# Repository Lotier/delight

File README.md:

# DELIGHT Keyboard

**65+% keyboard assembled with only through hole components, including usb type-c**
**65+% means there is an extra row at the top for the Escape key just for the delight of programmers.

**[LICENSE](LICENSE)**

DELIGHT Keyboard is licensed under the [Creative Commons Attribution-NonCommercial 4.0 International License](https://creativecommons.org/licenses/by-nc/4.0/). , this board is adapted from [coseyfannitutti Discipline](https://github.com/coseyfannitutti/discipline) work.

This PCB design may be freely reproduced, modified, and manufactured for **PERSONAL USE ONLY** and may not be reproduced in physical form for public sale. 

# Keyboard Layout Editor
http://www.keyboard-layout-editor.com/#/
```
[{a:7},"esc"],
["`","1","2","3","4","5","6","7","8","9","0","-","=",{w:2},"backspace","home"],
[{w:1.5},"tab","q","w","e","r","t","y","u","i","o","p","[","]",{w:1.5},"\\","pgup"],
[{w:1.75},"cap","a","s","d","f","g","h","j","k","l",";","'",{w:2.25},"enter","pgdn"],
[{w:2.25},"shift","z","x","c","v","b","n","m",",",".","/",{w:1.75},"shift","up","end"],
[{w:1.25},"ctrl",{w:1.25},"win",{w:1.25},"alt",{w:6.25},"","alt","fn","ctrl","left","down","right"]
```

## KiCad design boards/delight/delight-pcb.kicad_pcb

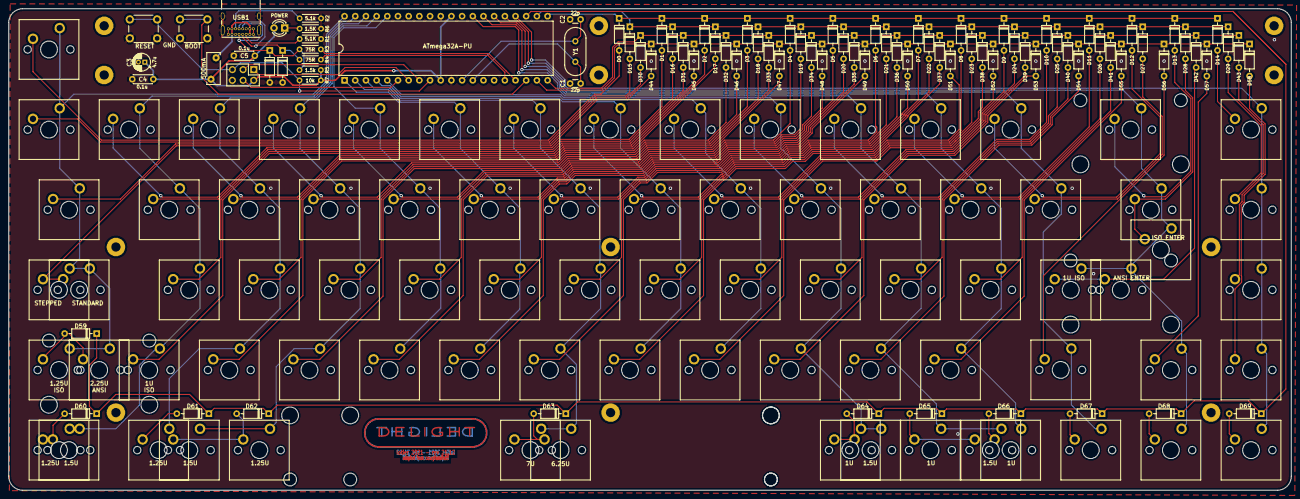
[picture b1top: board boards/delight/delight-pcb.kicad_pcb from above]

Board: 2 copper layers, 304.9 x 114.5 mm, 176 parts (0 on the bottom side), 107 nets.

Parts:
BOOT1: BOOT; SW_PUSH_6mm
C1, C2: 22p; C_Disc_D3.0mm_W1.6mm_P2.50mm
C3: 4.7u; CP_Radial_D4.0mm_P1.50mm
C4, C5: 0.1u; C_Disc_D4.3mm_W1.9mm_P5.00mm
D0, D1, D2, D3, D4, D5, D6, D7, D8, D9, D10, D11, D12, D13, D14, D15, D16, D17, D18, D19, D20, D21, D22, D23, D24, D25, D26, D27, D28, D29, D30, D31, D32, D33, D34, D35, D36, D37, D38, D39, D40, D41, D42, D43, D44, D45, D46, D47, D48, D49, D50, D51, D52, D53, D54, D55, D56, D57, D58, D59, D60, D61, D62, D63, D64, D65, D66, D67, D68, D69: D_DO-35_SOD27_P7.62mm_Horizontal
D70, D71: 3.6V; D_DO-35_SOD27_P7.62mm_Horizontal
F1: 500mA; Fuse_Bourns_MF-RHT050
J1: AVR-ISP-6; PinHeader_2x03_P2.54mm_Vertical
LED1: POWER; LED_D3.0mm
R1, R2: 5.1k; R_Axial_DIN0204_L3.6mm_D1.6mm_P5.08mm_Horizontal
R3, R4: 75R; R_Axial_DIN0204_L3.6mm_D1.6mm_P5.08mm_Horizontal
R5: 1.5k; R_Axial_DIN0204_L3.6mm_D1.6mm_P5.08mm_Horizontal
R6: 1.5K; R_Axial_DIN0204_L3.6mm_D1.6mm_P5.08mm_Horizontal
R7: 10k; R_Axial_DIN0204_L3.6mm_D1.6mm_P5.08mm_Horizontal
RESET1: RESET; SW_PUSH_6mm
ST13, ST42, ST59: Stabilizer_Cherry_MX_2u
ST63: 6.25U; Stabilizer_Cherry_MX_6.25u
ST63-2: 7U; Stabilizer_Cherry_MX_7u
SW0, SW1, SW2, SW3, SW4, SW5, SW6, SW7, SW8, SW9, SW10, SW11, SW12, SW14, SW15, SW16, SW17, SW18, SW19, SW20, SW21, SW22, SW23, SW24, SW25, SW26, SW27, SW29, SW31, SW32, SW33, SW34, SW35, SW36, SW37, SW38, SW39, SW40, SW41, SW42-2, SW43, SW45, SW46, SW47, SW48, SW49, SW50, SW51, SW52, SW53, SW54, SW55, SW57, SW58, SW64, SW65, SW66, SW67, SW68, SW69: KEYSW; SW_Cherry_MX_PCB_1.00u
SW13: KEYSW; SW_Cherry_MX_PCB_2.00u
SW28, SW30, SW60-2, SW62-2, SW64-2, SW65-2: KEYSW; SW_Cherry_MX_PCB_1.50u
SW28-2: KEYSW; SW_Cherry_MX_Plate_ISOEnter
SW42, SW59: KEYSW; SW_Cherry_MX_PCB_2.25u
SW44, SW56: KEYSW; SW_Cherry_MX_PCB_1.75u
SW44-2, SW59-2, SW60, SW61, SW62: KEYSW; SW_Cherry_MX_PCB_1.25u
SW63: KEYSW; SW_Cherry_MX_PCB_6.25u
SW63-2: KEYSW; SW_Cherry_MX_PCB_7.00u
U1: ATmega32A-PU; DIP-40_W15.24mm
USB1: USB_C_GCT_USB4085; USB_C_Receptacle_GCT_USB4085
Y1: Crystal; Crystal_HC49-4H_Vertical

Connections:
+5V: C3.1, C4.1, C5.1, F1.1, J1.2, LED1.2, R5.1, R7.1, U1.10, U1.30
D+: R4.1, U1.16
D-: R3.1, U1.17
GND: BOOT1.2, C1.2, C2.2, C3.2, C4.2, C5.2, D70.2, D71.2, J1.6, R1.1, R2.2, R6.2, RESET1.2, U1.11, U1.31, USB1.A1, USB1.A12, USB1.B1, USB1.B12, USB1.S1
MISO: J1.1, U1.7
MOSI: J1.4, U1.6
unnamed: C1.1, U1.13, Y1.1
unnamed: C2.1, U1.12, Y1.2
unnamed: D0.2, SW0.1
unnamed: D1.2, SW1.1
unnamed: D2.2, SW2.1
unnamed: D3.2, SW3.1
unnamed: D4.2, SW4.1
unnamed: D5.2, SW5.1
unnamed: D6.2, SW6.1
unnamed: D7.2, SW7.1
unnamed: D8.2, SW8.1
unnamed: D9.2, SW9.1
unnamed: D10.2, SW10.1
unnamed: D11.2, SW11.1
unnamed: D12.2, SW12.1
unnamed: D13.2, SW13.1
unnamed: D14.2, SW14.1
unnamed: D15.2, SW15.1
unnamed: D16.2, SW16.1
unnamed: D17.2, SW17.1
unnamed: D18.2, SW18.1
unnamed: D19.2, SW19.1
unnamed: D20.2, SW20.1
unnamed: D21.2, SW21.1
unnamed: D22.2, SW22.1
unnamed: D23.2, SW23.1
unnamed: D24.2, SW24.1
unnamed: D25.2, SW25.1
unnamed: D26.2, SW26.1
unnamed: D27.2, SW27.1
unnamed: D28.2, SW28.1, SW28-2.1
unnamed: D29.2, SW29.1
unnamed: D30.2, SW30.1
unnamed: D31.2, SW31.1
unnamed: D32.2, SW32.1
unnamed: D33.2, SW33.1
unnamed: D34.2, SW34.1
unnamed: D35.2, SW35.1
unnamed: D36.2, SW36.1
unnamed: D37.2, SW37.1
unnamed: D38.2, SW38.1
unnamed: D39.2, SW39.1
unnamed: D40.2, SW40.1
unnamed: D41.2, SW41.1
unnamed: D42.2, SW42.1, SW42-2.1
unnamed: D43.2, SW43.1
unnamed: D44.2, SW44.1, SW44-2.1
unnamed: D45.2, SW45.1
unnamed: D46.2, SW46.1
unnamed: D47.2, SW47.1
unnamed: D48.2, SW48.1
unnamed: D49.2, SW49.1
unnamed: D50.2, SW50.1
unnamed: D51.2, SW51.1
unnamed: D52.2, SW52.1
unnamed: D53.2, SW53.1
unnamed: D54.2, SW54.1
unnamed: D55.2, SW55.1
unnamed: D56.2, SW56.1
unnamed: D57.2, SW57.1
unnamed: D58.2, SW58.1
unnamed: D59.2, SW59.1, SW59-2.1
unnamed: D60.2, SW60.1, SW60-2.1
unnamed: D61.2, SW61.1
unnamed: D62.2, SW62.1, SW62-2.1
unnamed: D63.2, SW63.1, SW63-2.1
unnamed: D64.2, SW64.1, SW64-2.1
unnamed: D65.2, SW65.1, SW65-2.1
unnamed: D66.2, SW66.1
unnamed: D67.2, SW67.1
unnamed: D68.2, SW68.1
unnamed: D69.2, SW69.1
unnamed: D70.1, R3.2, R5.2, USB1.A7, USB1.B7
unnamed: D71.1, R4.2, USB1.A6, USB1.B6
unnamed: LED1.1, R6.1
unnamed: R1.2, USB1.A5
unnamed: R2.1, USB1.B5
SCK: J1.3, U1.8
VCC: F1.2, USB1.A4, USB1.A9, USB1.B4, USB1.B9
boot: BOOT1.1, U1.18
col0: SW0.2, SW15.2, SW30.2, SW44.2, SW44-2.2, SW59.2, SW59-2.2, U1.40
col1: SW1.2, SW16.2, SW31.2, SW45.2, SW60.2, SW60-2.2, U1.39
col2: SW2.2, SW17.2, SW32.2, SW46.2, SW61.2, U1.38
col3: SW3.2, SW18.2, SW33.2, SW47.2, SW62.2, SW62-2.2, U1.37
col4: SW4.2, SW19.2, SW34.2, SW48.2, U1.36
col5: SW5.2, SW20.2, SW35.2, SW49.2, U1.1
col6: SW6.2, SW21.2, SW36.2, SW50.2, SW63.2, SW63-2.2, U1.2
col7: SW7.2, SW22.2, SW37.2, SW51.2, U1.3
col8: SW8.2, SW23.2, SW38.2, SW52.2, U1.4
col9: SW9.2, SW24.2, SW39.2, SW53.2, SW64.2, SW64-2.2, U1.5
col10: SW10.2, SW25.2, SW40.2, SW54.2, SW65.2, SW65-2.2, U1.28
col11: SW11.2, SW26.2, SW41.2, SW55.2, SW66.2, U1.27
col12: SW12.2, SW27.2, SW56.2, SW67.2, U1.26
col13: SW13.2, SW28.2, SW28-2.2, SW42.2, SW42-2.2, SW57.2, SW68.2, U1.25
col14: SW14.2, SW29.2, SW43.2, SW58.2, SW69.2, U1.24
reset: J1.5, R7.2, RESET1.1, U1.9
row0: D0.1, D1.1, D2.1, D3.1, D4.1, D5.1, D6.1, D7.1, D8.1, D9.1, D10.1, D11.1, D12.1, D13.1, D14.1, U1.21
row1: D15.1, D16.1, D17.1, D18.1, D19.1, D20.1, D21.1, D22.1, D23.1, D24.1, D25.1, D26.1, D27.1, D28.1, D29.1, U1.22
row2: D30.1, D31.1, D32.1, D33.1, D34.1, D35.1, D36.1, D37.1, D38.1, D39.1, D40.1, D41.1, D42.1, D43.1, U1.20
row3: D44.1, D45.1, D46.1, D47.1, D48.1, D49.1, D50.1, D51.1, D52.1, D53.1, D54.1, D55.1, D56.1, D57.1, D58.1, U1.19
row4: D59.1, D60.1, D61.1, D62.1, D63.1, D64.1, D65.1, D66.1, D67.1, D68.1, D69.1, U1.23

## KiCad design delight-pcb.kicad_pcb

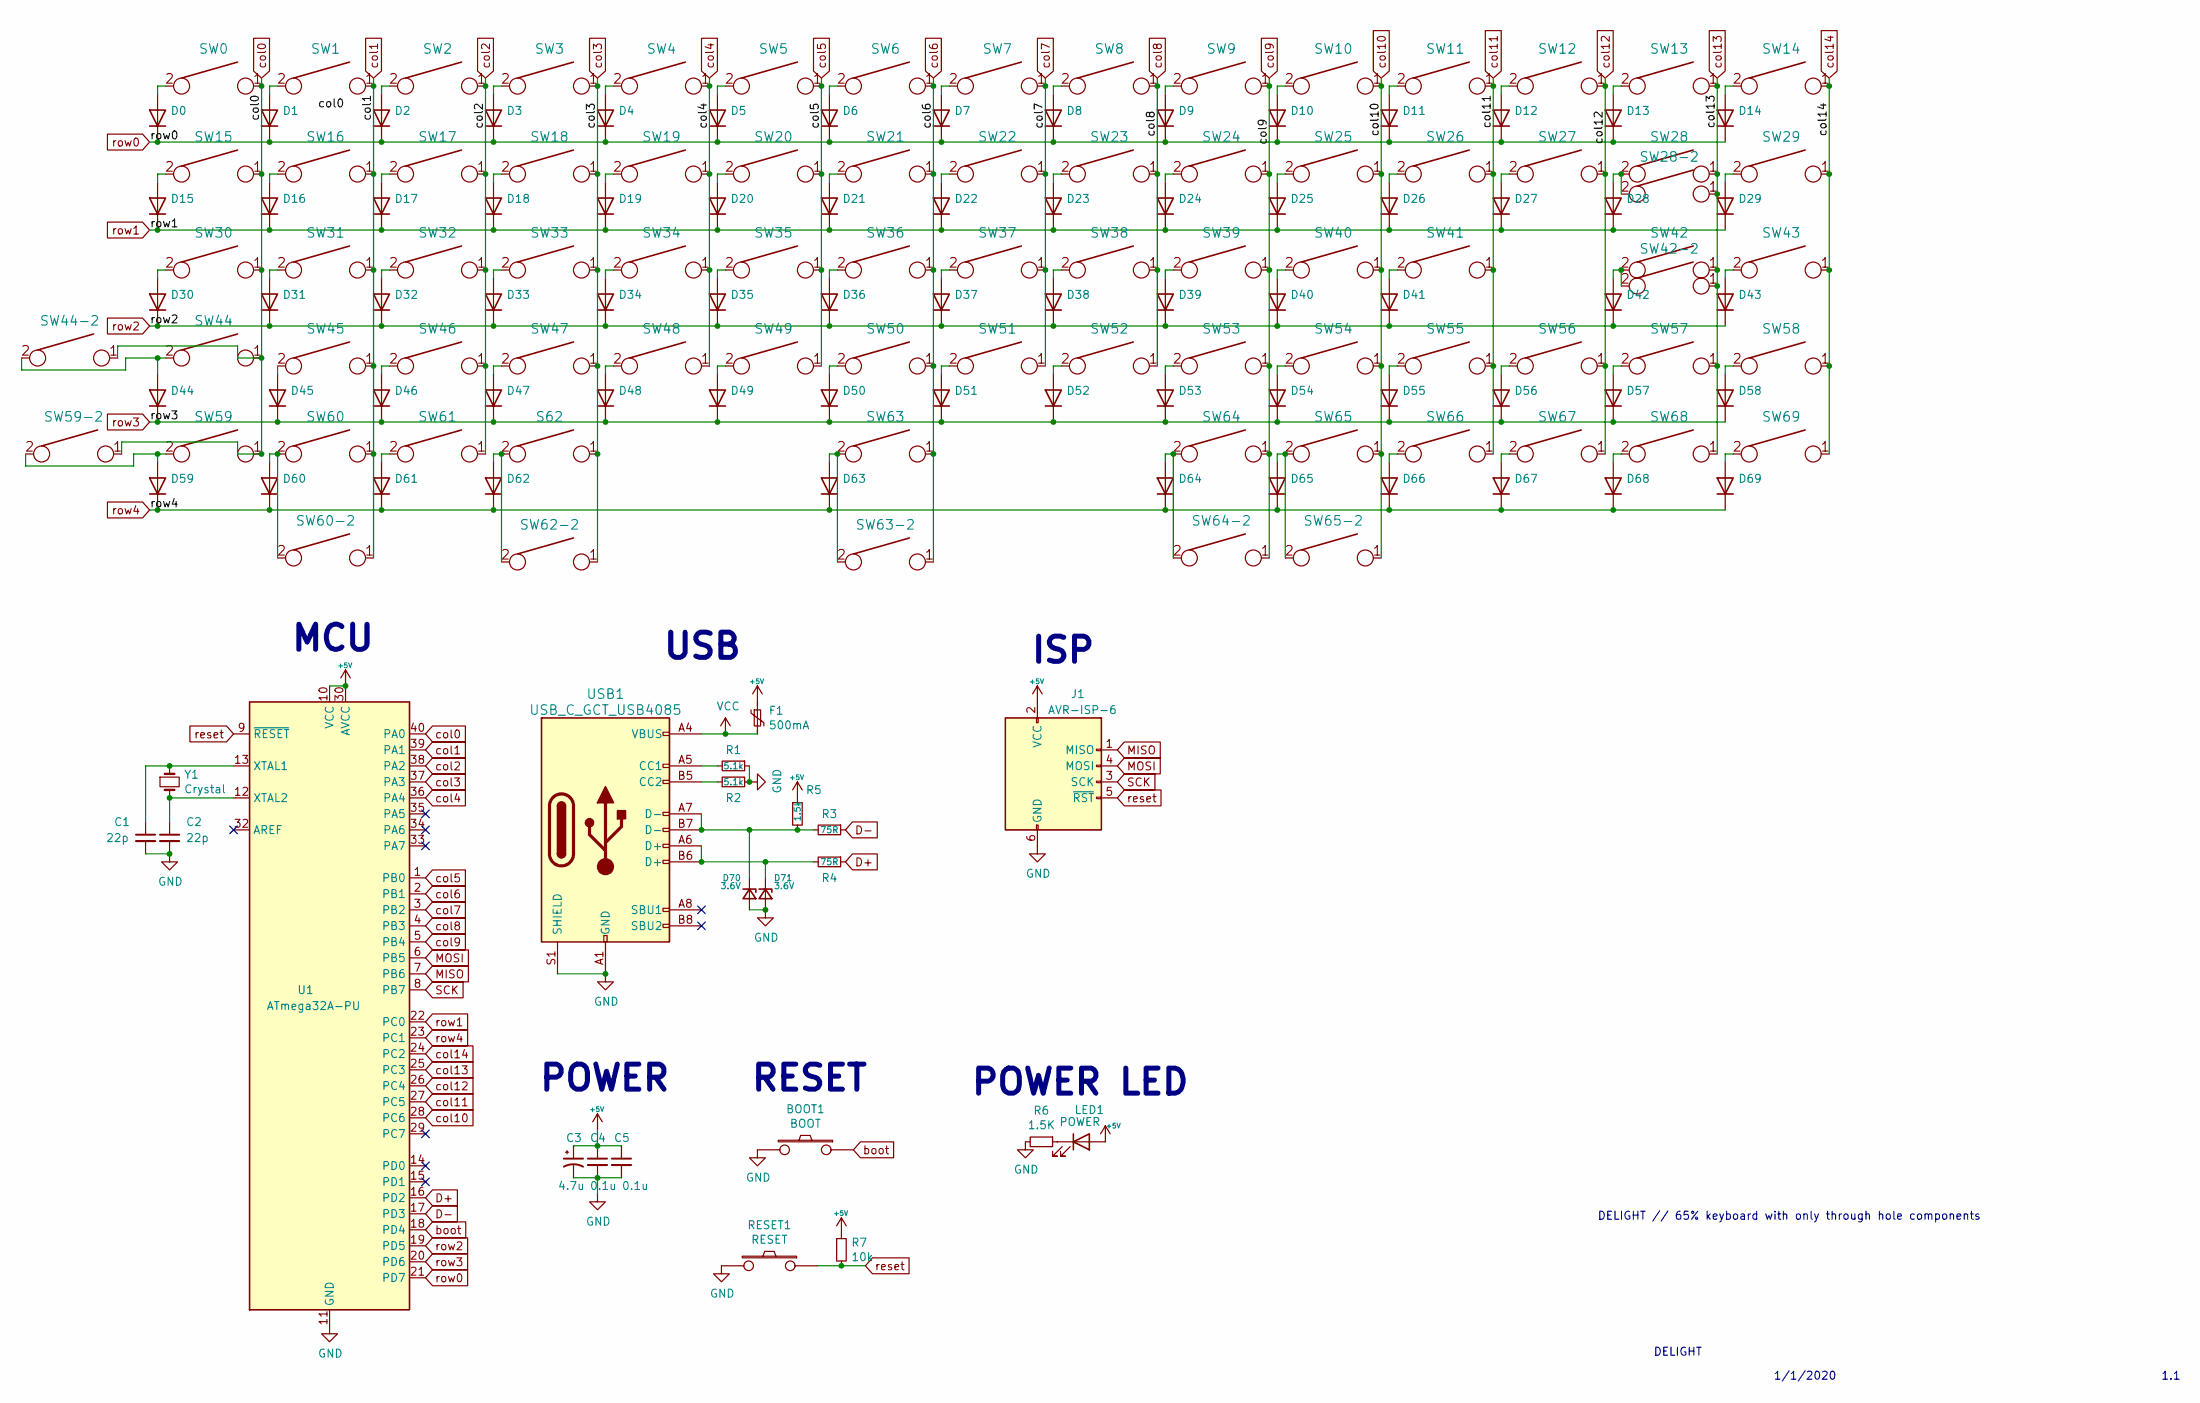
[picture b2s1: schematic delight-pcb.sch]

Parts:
BOOT1: BOOT; SW_PUSH_6mm
C1, C2: 22p; C_Disc_D3.0mm_W1.6mm_P2.50mm
C3: 4.7u; CP_Radial_D4.0mm_P1.50mm
C4, C5: 0.1u; C_Disc_D4.3mm_W1.9mm_P5.00mm
D0, D1, D2, D3, D4, D5, D6, D7, D8, D9, D10, D11, D12, D13, D14, D15, D16, D17, D18, D19, D20, D21, D22, D23, D24, D25, D26, D27, D28, D29, D30, D31, D32, D33, D34, D35, D36, D37, D38, D39, D40, D41, D42, D43, D44, D45, D46, D47, D48, D49, D50, D51, D52, D53, D54, D55, D56, D57, D58, D59, D60, D61, D62, D63, D64, D65, D66, D67, D68, D69: D_DO-35_SOD27_P5.08mm_Horizontal
D70, D71: 3.6V; D_DO-35_SOD27_P5.08mm_Horizontal
F1: 500mA; polyfuse_5.1mm
J1: AVR-ISP-6; AVR_ICSP_3x2
LED1: POWER; LED_D3.0mm
R1, R2: 5.1k; R_Axial_DIN0204_L3.6mm_D1.6mm_P5.08mm_Horizontal
R3, R4: 75R; R_Axial_DIN0204_L3.6mm_D1.6mm_P5.08mm_Horizontal
R5: 1.5k; R_Axial_DIN0204_L3.6mm_D1.6mm_P5.08mm_Horizontal
R6: 1.5K; R_Axial_DIN0204_L3.6mm_D1.6mm_P5.08mm_Horizontal
R7: 10k; R_Axial_DIN0204_L3.6mm_D1.6mm_P5.08mm_Horizontal
RESET1: RESET; SW_PUSH_6mm
S62: KEYSW; SW_Cherry_MX1A_1.25u_PCBNOSCREEN
SW0, SW1, SW2, SW3, SW4, SW5, SW6, SW7, SW8, SW9, SW10, SW11, SW12, SW14, SW15, SW16, SW17, SW18, SW19, SW20, SW21, SW22, SW23, SW24, SW25, SW26, SW27, SW29, SW31, SW32, SW33, SW34, SW35, SW36, SW37, SW38, SW39, SW40, SW41, SW42-2, SW43, SW45, SW46, SW47, SW48, SW49, SW50, SW51, SW52, SW53, SW54, SW55, SW57, SW58, SW63, SW63-2, SW66, SW67, SW68, SW69: KEYSW; SW_Cherry_MX1A_1.00u_PCB-NOSCREEN
SW13: KEYSW; SW_Cherry_MX1A_2.00u_PCBNOSCREEN
SW28, SW30, SW60-2, SW62-2, SW64-2, SW65-2: KEYSW; SW_Cherry_MX1A_1.50u_PCBNOSCREEN
SW28-2: KEYSW; SW_Cherry_MX1A_ISOEnter_PCB_ReversedStabilizer
SW42, SW59: KEYSW; SW_Cherry_MX1A_2.25u_PCBNOSCREEN
SW44, SW56: KEYSW; SW_Cherry_MX1A_1.75u_PCBNOSCREEN
SW44-2, SW59-2, SW60, SW61, SW64, SW65: KEYSW; SW_Cherry_MX1A_1.25u_PCBNOSCREEN
U1: ATmega32A-PU; DIP-40_W15.24mm
USB1: USB_C_GCT_USB4085
Y1: Crystal; Crystal_HC49-4H_Vertical

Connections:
+5V: C3.1, C4.1, C5.1, F1.1, J1.2 (VCC), LED1.2 (A), R5.1, R7.1, U1.10 (VCC), U1.30 (AVCC)
D+: R4.1, U1.16 (PD2)
D-: R3.1, U1.17 (PD3)
GND: BOOT1.2, C1.2, C2.2, C3.2, C4.2, C5.2, D70.2 (A), D71.2 (A), J1.6 (GND), R1.1, R2.2, R6.2, RESET1.2, U1.11 (GND), U1.31 (GND), USB1.A1 (GND), USB1.A12 (GND), USB1.B1 (GND), USB1.B12 (GND), USB1.S1 (SHIELD)
MISO: J1.1 (MISO), U1.7 (PB6)
MOSI: J1.4 (MOSI), U1.6 (PB5)
unnamed: C1.1, U1.13 (XTAL1), Y1.1
unnamed: C2.1, U1.12 (XTAL2), Y1.2
unnamed: D0.2 (A), SW0.2
unnamed: D1.2 (A), SW1.2
unnamed: D2.2 (A), SW2.2
unnamed: D3.2 (A), SW3.2
unnamed: D4.2 (A), SW4.2
unnamed: D5.2 (A), SW5.2
unnamed: D6.2 (A), SW6.2
unnamed: D7.2 (A), SW7.2
unnamed: D8.2 (A), SW8.2
unnamed: D9.2 (A), SW9.2
unnamed: D10.2 (A), SW10.2
unnamed: D11.2 (A), SW11.2
unnamed: D12.2 (A), SW12.2
unnamed: D13.2 (A), SW13.2
unnamed: D14.2 (A), SW14.2
unnamed: D15.2 (A), SW15.2
unnamed: D16.2 (A), SW16.2
unnamed: D17.2 (A), SW17.2
unnamed: D18.2 (A), SW18.2
unnamed: D19.2 (A), SW19.2
unnamed: D20.2 (A), SW20.2
unnamed: D21.2 (A), SW21.2
unnamed: D22.2 (A), SW22.2
unnamed: D23.2 (A), SW23.2
unnamed: D24.2 (A), SW24.2
unnamed: D25.2 (A), SW25.2
unnamed: D26.2 (A), SW26.2
unnamed: D27.2 (A), SW27.2
unnamed: D28.2 (A), SW28.2, SW28-2.2
unnamed: D29.2 (A), SW29.2
unnamed: D30.2 (A), SW30.2
unnamed: D31.2 (A), SW31.2
unnamed: D32.2 (A), SW32.2
unnamed: D33.2 (A), SW33.2
unnamed: D34.2 (A), SW34.2
unnamed: D35.2 (A), SW35.2
unnamed: D36.2 (A), SW36.2
unnamed: D37.2 (A), SW37.2
unnamed: D38.2 (A), SW38.2
unnamed: D39.2 (A), SW39.2
unnamed: D40.2 (A), SW40.2
unnamed: D41.2 (A), SW41.2
unnamed: D42.2 (A), SW42.2, SW42-2.2
unnamed: D43.2 (A), SW43.2
unnamed: D44.2 (A), SW44.2, SW44-2.2
unnamed: D45.2 (A), SW45.2
unnamed: D46.2 (A), SW46.2
unnamed: D47.2 (A), SW47.2
unnamed: D48.2 (A), SW48.2
unnamed: D49.2 (A), SW49.2
unnamed: D50.2 (A), SW50.2
unnamed: D51.2 (A), SW51.2
unnamed: D52.2 (A), SW52.2
unnamed: D53.2 (A), SW53.2
unnamed: D54.2 (A), SW54.2
unnamed: D55.2 (A), SW55.2
unnamed: D56.2 (A), SW56.2
unnamed: D57.2 (A), SW57.2
unnamed: D58.2 (A), SW58.2
unnamed: D59.2 (A), SW59.2, SW59-2.2
unnamed: D60.2 (A), SW60.2, SW60-2.2
unnamed: D61.2 (A), SW61.2
unnamed: D62.2 (A), S62.2, SW62-2.2
unnamed: D63.2 (A), SW63.2, SW63-2.2
unnamed: D64.2 (A), SW64.2, SW64-2.2
unnamed: D65.2 (A), SW65.2, SW65-2.2
unnamed: D66.2 (A), SW66.2
unnamed: D67.2 (A), SW67.2
unnamed: D68.2 (A), SW68.2
unnamed: D69.2 (A), SW69.2
unnamed: D70.1 (K), R3.2, R5.2, USB1.A7 (D-), USB1.B7 (D-)
unnamed: D71.1 (K), R4.2, USB1.A6 (D+), USB1.B6 (D+)
unnamed: LED1.1 (K), R6.1
unnamed: R1.2, USB1.A5 (CC1)
unnamed: R2.1, USB1.B5 (CC2)
SCK: J1.3 (SCK), U1.8 (PB7)
VCC: F1.2, USB1.A4 (VBUS), USB1.A9 (VBUS), USB1.B4 (VBUS), USB1.B9 (VBUS)
boot: BOOT1.1, U1.18 (PD4)
col0: SW0.1, SW15.1, SW30.1, SW44.1, SW44-2.1, SW59.1, SW59-2.1, U1.40 (PA0)
col1: SW1.1, SW16.1, SW31.1, SW45.1, SW60.1, SW60-2.1, U1.39 (PA1)
col2: SW2.1, SW17.1, SW32.1, SW46.1, SW61.1, U1.38 (PA2)
col3: S62.1, SW3.1, SW18.1, SW33.1, SW47.1, SW62-2.1, U1.37 (PA3)
col4: SW4.1, SW19.1, SW34.1, SW48.1, U1.36 (PA4)
col5: SW5.1, SW20.1, SW35.1, SW49.1, U1.1 (PB0)
col6: SW6.1, SW21.1, SW36.1, SW50.1, SW63.1, SW63-2.1, U1.2 (PB1)
col7: SW7.1, SW22.1, SW37.1, SW51.1, U1.3 (PB2)
col8: SW8.1, SW23.1, SW38.1, SW52.1, U1.4 (PB3)
col9: SW9.1, SW24.1, SW39.1, SW53.1, SW64.1, SW64-2.1, U1.5 (PB4)
col10: SW10.1, SW25.1, SW40.1, SW54.1, SW65.1, SW65-2.1, U1.28 (PC6)
col11: SW11.1, SW26.1, SW41.1, SW55.1, SW66.1, U1.27 (PC5)
col12: SW12.1, SW27.1, SW56.1, SW67.1, U1.26 (PC4)
col13: SW13.1, SW28.1, SW28-2.1, SW42.1, SW42-2.1, SW57.1, SW68.1, U1.25 (PC3)
col14: SW14.1, SW29.1, SW43.1, SW58.1, SW69.1, U1.24 (PC2)
reset: J1.5 (~RST), R7.2, RESET1.1, U1.9 (~RESET)
row0: D0.1 (K), D1.1 (K), D2.1 (K), D3.1 (K), D4.1 (K), D5.1 (K), D6.1 (K), D7.1 (K), D8.1 (K), D9.1 (K), D10.1 (K), D11.1 (K), D12.1 (K), D13.1 (K), D14.1 (K), U1.21 (PD7)
row1: D15.1 (K), D16.1 (K), D17.1 (K), D18.1 (K), D19.1 (K), D20.1 (K), D21.1 (K), D22.1 (K), D23.1 (K), D24.1 (K), D25.1 (K), D26.1 (K), D27.1 (K), D28.1 (K), D29.1 (K), U1.22 (PC0)
row2: D30.1 (K), D31.1 (K), D32.1 (K), D33.1 (K), D34.1 (K), D35.1 (K), D36.1 (K), D37.1 (K), D38.1 (K), D39.1 (K), D40.1 (K), D41.1 (K), D42.1 (K), D43.1 (K), U1.19 (PD5)
row3: D44.1 (K), D45.1 (K), D46.1 (K), D47.1 (K), D48.1 (K), D49.1 (K), D50.1 (K), D51.1 (K), D52.1 (K), D53.1 (K), D54.1 (K), D55.1 (K), D56.1 (K), D57.1 (K), D58.1 (K), U1.20 (PD6)
row4: D59.1 (K), D60.1 (K), D61.1 (K), D62.1 (K), D63.1 (K), D64.1 (K), D65.1 (K), D66.1 (K), D67.1 (K), D68.1 (K), D69.1 (K), U1.23 (PC1)

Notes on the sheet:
DELIGHT // 65% keyboard with only through hole components
1/1/2020
DELIGHT
1.1
MCU
USB
ISP
POWER
RESET
POWER LED

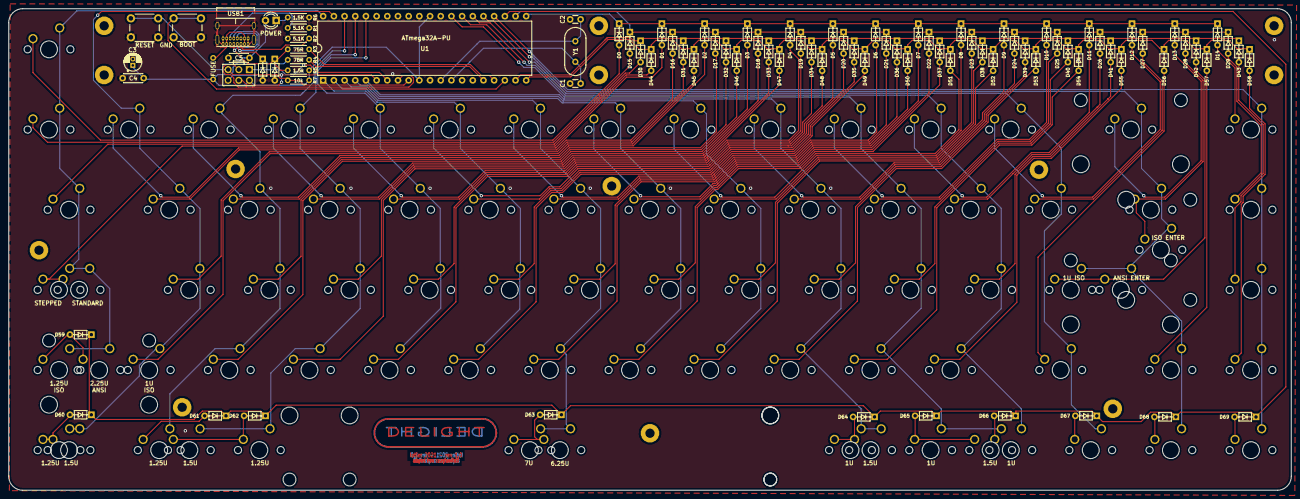
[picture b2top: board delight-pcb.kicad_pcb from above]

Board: 2 copper layers, 304.9 x 114.5 mm, 172 parts (0 on the bottom side), 107 nets.

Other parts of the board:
ST72: 7U; MX-7U-Stabilizer

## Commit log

2021-06-25 Base design of Delight Keyboard
    All traces are connected, it's not pretty, but it would work.
2021-06-26 Front Side Cleanup
    All major row/column wires are in a great spot now.
2021-06-27 Last cleanup of placements.
2021-06-27 More trace design
    No more messing with it.
2021-06-28 Wrapping Up
    Finished up all major tasks.
2021-06-28 Remove ignored files
2021-07-01 Created Switch Plate
2021-07-01 Cleanup of Files
    Just removing a bunch of the files.
2021-07-01 Attempted Project Rename
    Attempting to rename the project.
2021-07-01 Renaming Continued
2021-07-01 Renaming Complete
    Finishing off all the renaming.
2021-07-30 Uploading the first image
2021-08-10 Uploading Bootloader Directions
2021-08-11 Adding Low Profile Case Design
2021-08-11 Added Low Profile Plate Design
    * Fixup project structure.
2021-08-17 Adding components plate cover
2021-08-17 Move Readme to proper location
2021-08-18 Start Process to design hotswap
2021-08-18 Submodule cleanpu
2021-08-18 Add kicad library as submodules
2021-08-19 Startup For Using standard library
2021-08-19 continue doc update
2021-08-27 Swapped out as many custom mods for standard.
2021-08-27 Fixing the plate, since I can't do math.
2021-10-10 Cleanup of Plate Layout
2021-10-10 Cleaning up layout.
2021-10-10 Updated all routes.
2021-10-11 More cleanup
2021-10-11 Adding Stabs back in.
2021-10-11 Cleanup all the tracks after the footprint switch.
2021-10-12 Traces for power and pairs
2021-10-12 Footprint schema updated
2021-10-12 Once more with layouts
2021-10-12 mounting holes movement.
2021-10-12 More project cleanup
2021-10-13 Final Cleanup
2021-10-14 Hotswap created and routed
2021-10-15 Reorg of project layout
2021-10-15 proper submodule references
2021-10-15 Detach - And project update (#2)
    * Add missing keyboard_parts.lib, fix symbol refs in schematic
    * Fix broken ref Y1 on pcb
    * Base design of Delight Keyboard
    All traces are connected, it's not pretty, but it would work.
    * Front Side Cleanup
    All major row/column wires are in a great spot now.
2021-10-15 Create a cherry stab only plate.
    Hopefully for better creation of the board that breaks less on the think parts.
2021-10-16 Add Octopart BOM to doc readme.
2021-10-17 Fixed up 3D reference for stabilizers
2021-10-18 update submodule reference.
2021-12-05 Updating the Low Profile Case
2021-12-05 Update Version Name
2021-12-05 Drop the post .1 millimeter to match PCB thickness.
